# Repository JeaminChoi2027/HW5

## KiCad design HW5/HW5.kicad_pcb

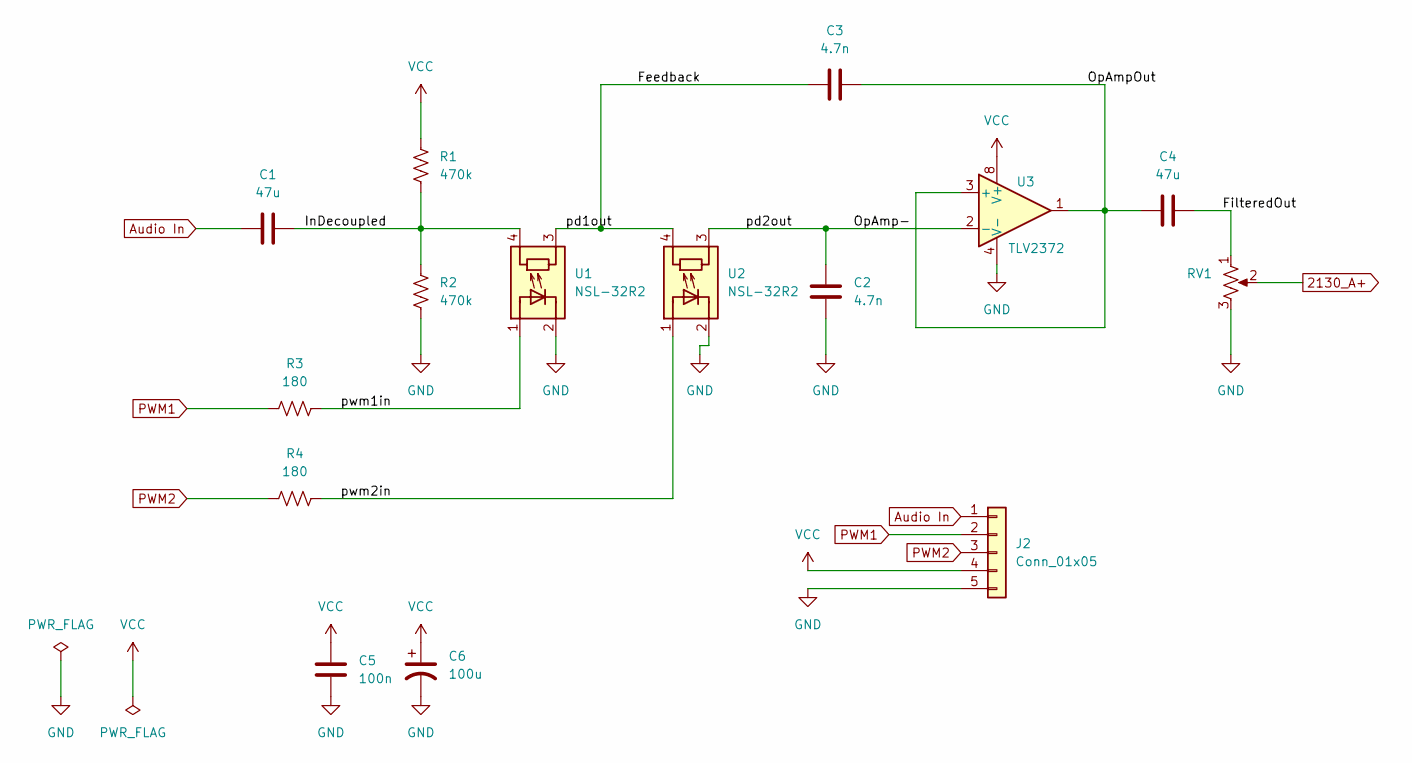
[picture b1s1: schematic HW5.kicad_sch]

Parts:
C1, C4: 47u; c1c4
C2, C3: 4.7n; c2c3
C5: 100n; c7
C6: 100u; CP_Radial_D5.0mm_P2.00mm
J2: Conn_01x05; PinHeader_1x05_P1.00mm_Horizontal
R1, R2: 470k; R_Axial_DIN0309_L9.0mm_D3.2mm_P25.40mm_Horizontal
R3, R4: 180; R_Axial_DIN0309_L9.0mm_D3.2mm_P25.40mm_Horizontal
RV1: R_Potentiometer_US; Potentiometer_Bourns_PTV09A-1_Single_Vertical
U1, U2: NSL-32R2; Luna_NSL-32
U3: TLV2372; DIP-8_W7.62mm_Socket

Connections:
2130_A+: RV1.2
/Feedback: C3.1, U1.3 (R), U2.4 (R)
/FilteredOut: C4.2, RV1.1
/InDecoupled: C1.2, R1.2, R2.1, U1.4 (R)
/OpAmp-: C2.1, U2.3 (R), U3.2 (-)
/OpAmpOut: C3.2, C4.1, U3.1 (NC), U3.3 (+)
/pwm1in: R3.2, U1.1 (A)
/pwm2in: R4.2, U2.1 (A)
Audio In: C1.1, J2.1
GND: C2.2, C5.2, C6.2, J2.5, R2.2, RV1.3, U1.2 (K), U2.2 (K), U3.4 (V-)
PWM1: J2.2, R3.1
PWM2: J2.3, R4.1
VCC: C5.1, C6.1, J2.4, R1.1, U3.8 (V+)

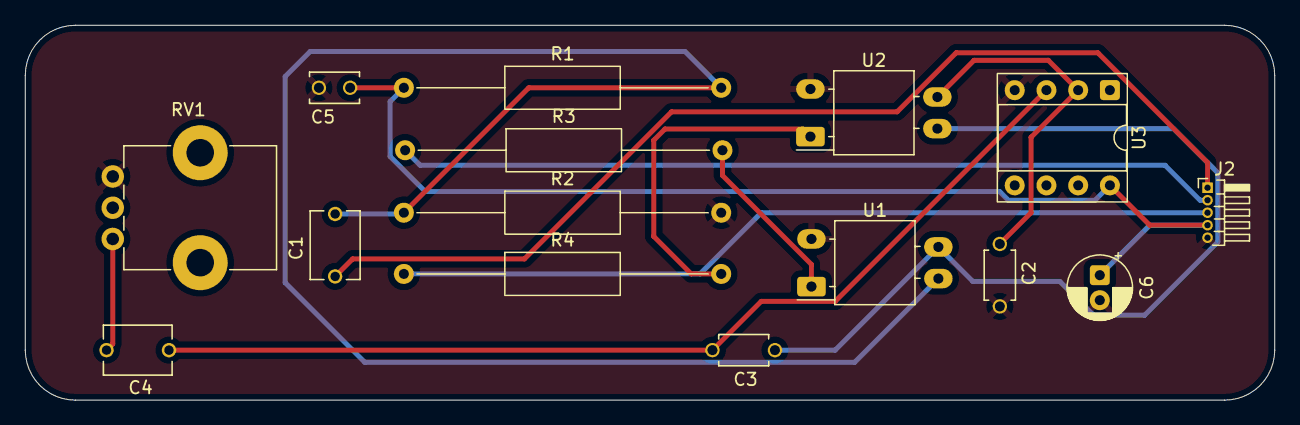
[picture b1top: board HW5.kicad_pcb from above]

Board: 2 copper layers, 100.0 x 30.0 mm, 15 parts (0 on the bottom side), 12 nets.

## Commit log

2026-03-02 day 1 work
2026-03-06 Add files via upload
    Changed opamp symbol + added 1x02 pinheader for 2in+ and 2out
    Added dimensions, shifted some text
